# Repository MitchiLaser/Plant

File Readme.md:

# automatic watering setup for a plant

This repository provides an electronic circuit board to water a plant. Is is driven by a microcontroller, an Attiny85, which gets the moldness of the soil in the pot from a sensor and powers a pump when it gets to dry.

In this repository you can find an electronic circuit board, designed in KiCad, as long as a firmware for the MCU and a 3d printable case. More documentation can be found on [my website](https://www.spice-space.de/inhalt/Pflanzenbewaesserung/index.html)

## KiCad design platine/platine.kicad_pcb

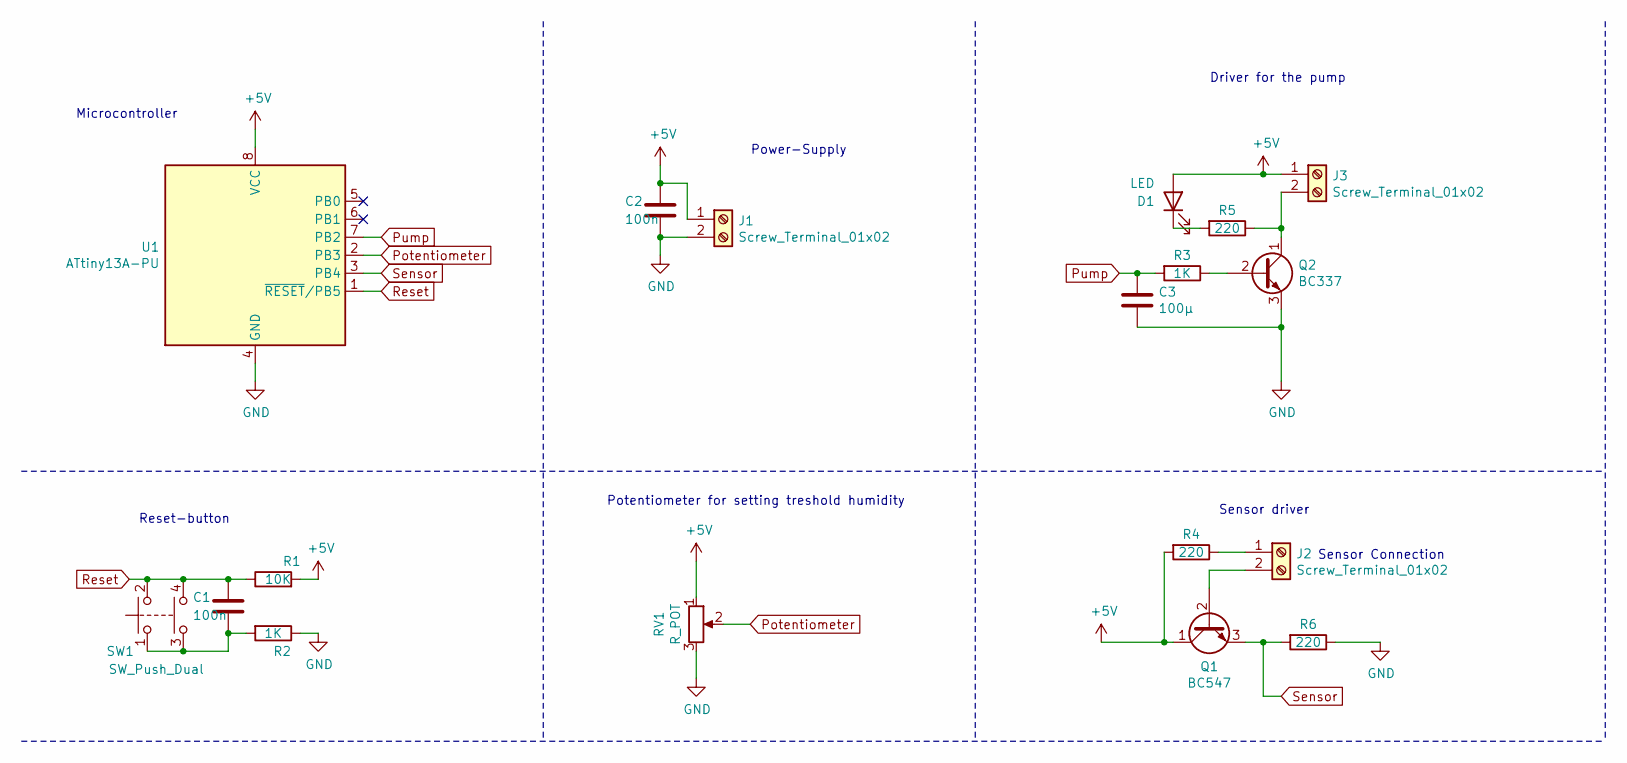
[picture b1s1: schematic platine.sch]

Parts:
C1, C2: 100n; C_Disc_D6.0mm_W2.5mm_P5.00mm
C3: 100µ; CP_Radial_D5.0mm_P2.50mm
D1: LED; LED_D5.0mm
J1, J2, J3: Screw_Terminal_01x02; TerminalBlock_Phoenix_MKDS-1,5-2-5.08_1x02_P5.08mm_Horizont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
Q1: BC547; TO-92_Inline
Q2: BC337; TO-92_Inline
R1: 10K; R_Axial_DIN0207_L6.3mm_D2.5mm_P7.62mm_Horizontal
R2, R3: 1K; R_Axial_DIN0207_L6.3mm_D2.5mm_P7.62mm_Horizontal
R4, R5, R6: 220; R_Axial_DIN0207_L6.3mm_D2.5mm_P7.62mm_Horizontal
RV1: R_POT; Potentiometer_Alps_RK163_Single_Horizontal
SW1: SW_Push_Dual; SW_TH_Tactile_Omron_B3F-10xx
U1: ATtiny13A-PU; DIP-8_W7.62mm

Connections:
+5V: C2.1, D1.2 (A), J1.1, J3.1, Q1.1 (C), R1.2, R4.2, RV1.1, U1.8 (VCC)
GND: C2.2, C3.2, J1.2, Q2.3 (E), R2.1, R6.1, RV1.3, U1.4 (GND)
unnamed: C1.2, R2.2, SW1.1, SW1.3
unnamed: D1.1 (K), R5.2
unnamed: J2.1, R4.1
unnamed: J2.2, Q1.2 (B)
unnamed: J3.2, Q2.1 (C), R5.1
unnamed: Q2.2 (B), R3.1
Potentiometer: RV1.2, U1.2 (PB3)
Pump: C3.1, R3.2, U1.7 (PB2)
Reset: C1.1, R1.1, SW1.2, SW1.4, U1.1 (~RESET~/PB5)
Sensor: Q1.3 (E), R6.2, U1.3 (PB4)

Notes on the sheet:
Microcontroller
Power-Supply
Driver for the pump
Reset-button
Potentiometer for setting treshold humidity
Sensor Connection
Sensor driver

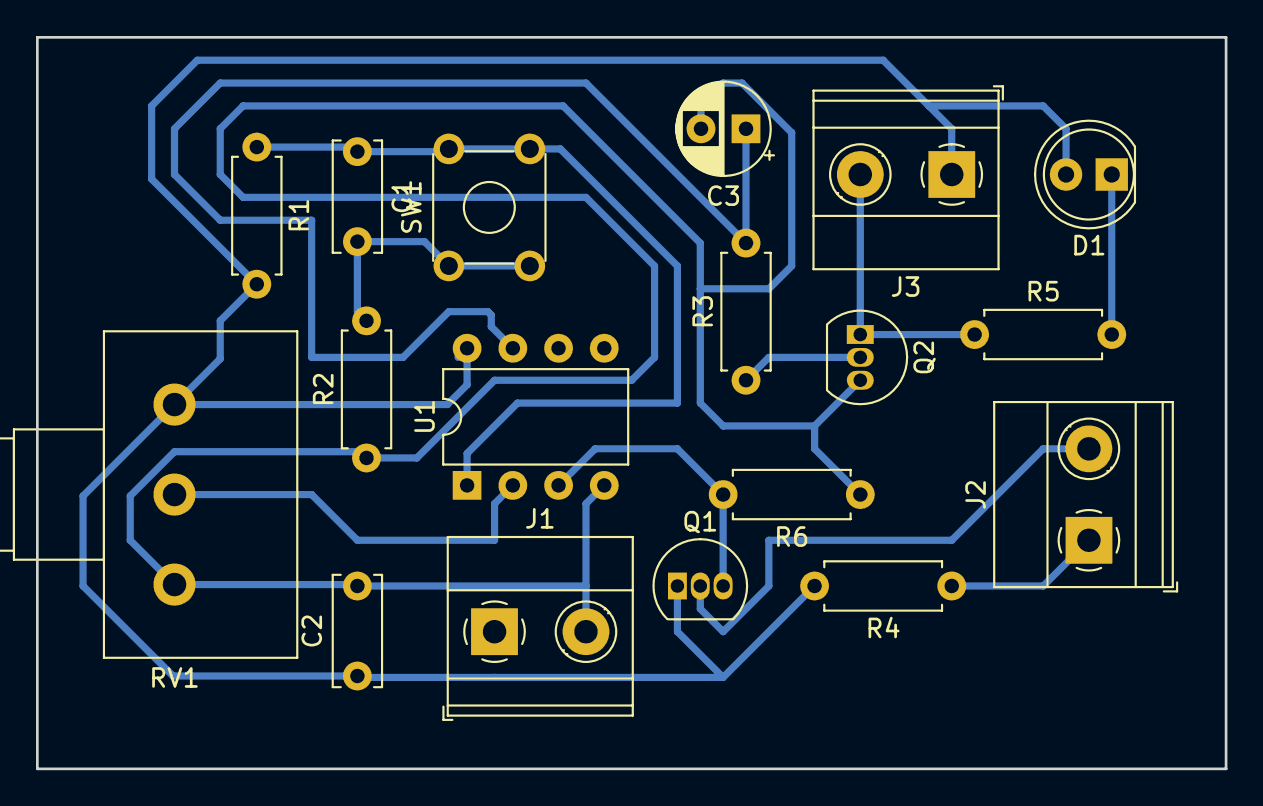
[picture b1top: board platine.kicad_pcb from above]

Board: 2 copper layers, 66.0 x 40.6 mm, 18 parts (0 on the bottom side), 12 nets.

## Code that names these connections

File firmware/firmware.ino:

// configuration
#define ADC_in A2 // pin connected to the analog moisture sensor
#define Pump_Out 2 // pin connected to the transistor, driving the pump
#define Pot_in A3 // the pin connected to the potentiometer

unsigned long last_Poll, wait;

void setup() {
  // drive pin connected to the moisture sensor and the potentiometer as input
  pinMode(ADC_in, INPUT);
  pinMode(Pot_in, INPUT);

  // drive pin connected to the transistor as output and close the transistor
  pinMode(Pump_Out, OUTPUT);
  digitalWrite(Pump_Out, HIGH);
  last_Poll = millis();

  wait = 1000; // wait 1000 milliseconds for every sensor check , equals 1 second
}

void loop() {

  if ( (millis() - wait) > last_Poll ) {
    last_Poll = millis();

    // get the value from the moisture sensor
    unsigned int Sensor_value = 0;
    for (unsigned int i = 0; i < 10; i++) {
      Sensor_value += analogRead(ADC_in);
    }
    Sensor_value /= 10;

    // get the value from the potentiometer
    unsigned int Pot_value = 0;
    for (unsigned int i = 0; i < 10; i++) {
      Pot_value += analogRead(Pot_in);
    }
    Pot_value /= 10;

    // if sensor value is smaller then potentiometer value then the earth is to dry -> water it
    if (Sensor_value < Pot_value) {
      digitalWrite(Pump_Out, HIGH);
    } else {
      digitalWrite(Pump_Out, LOW);
    }
  }
}

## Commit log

2021-04-28 Firmware V0.1
2021-04-29 Platine design: pump driver, power supply, reset-button, potentiometer
2021-05-01 Firmware timer-based and removed unnecessaries from scematics
2021-05-01 scematics ready
2021-05-01 pcb footprints assigned
2021-05-01 PCB Design done
2021-05-01 small optimisations on PCB
2021-05-02 small PCB donr
2021-05-02 small PCB done
2021-05-02 corrected pin assignment in firmware
2021-05-02 corrected wrong pin assignment in firmware
2021-05-02 3d-printable case
2021-05-03 provided readme
2021-05-03 case: improved lid
2021-05-06 Firmware: software-fix for hardware issue
2021-05-06 PCB: Added capacitor to smooth signal
